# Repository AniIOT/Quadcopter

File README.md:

# Quadcopter
All files related to the quadcopter project will be added here, which include mechanical drawings, cad files, datasheets for motors, PCB designs, gerber files, component datasheets and footprint files, software files, libraries, reference docs etc.

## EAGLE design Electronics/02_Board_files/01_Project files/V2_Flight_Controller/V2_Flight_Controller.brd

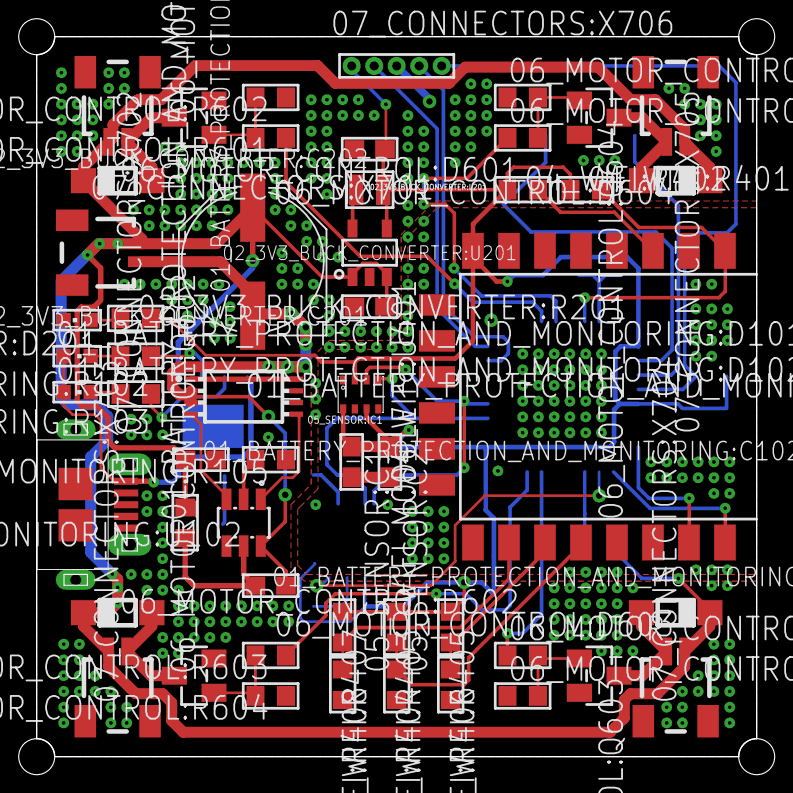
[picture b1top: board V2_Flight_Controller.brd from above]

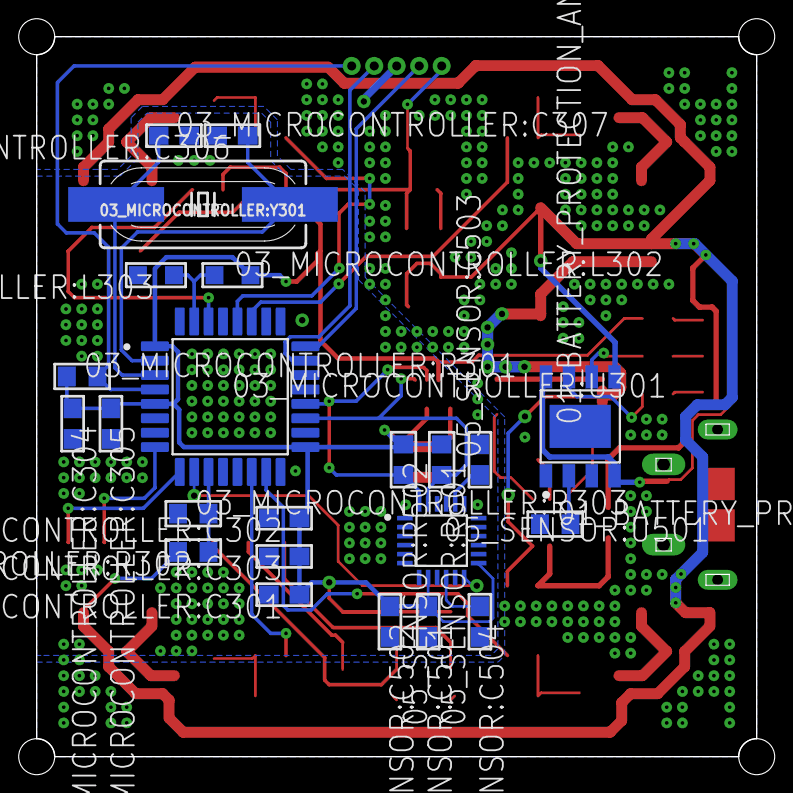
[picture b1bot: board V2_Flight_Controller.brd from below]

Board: 2 copper layers, 40.0 x 40.0 mm, 75 parts (23 on the bottom side), 48 nets.

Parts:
01_BATTERY_PROTECTION_AND_MONITORING:C101: 220uF; PANASONIC_E
01_BATTERY_PROTECTION_AND_MONITORING:C102, 02_3V3_BUCK_CONVERTER:C202: 10uF; C0603
01_BATTERY_PROTECTION_AND_MONITORING:C103: 0.1uF; C0603
01_BATTERY_PROTECTION_AND_MONITORING:D101: STDBY_GREEN; CHIPLED_0603
01_BATTERY_PROTECTION_AND_MONITORING:D102: CHRG_RED; CHIPLED_0603
01_BATTERY_PROTECTION_AND_MONITORING:R101: 4.8KΩ; R0603
01_BATTERY_PROTECTION_AND_MONITORING:R102, 01_BATTERY_PROTECTION_AND_MONITORING:R103, 01_BATTERY_PROTECTION_AND_MONITORING:R105, 02_3V3_BUCK_CONVERTER:R201, 06_MOTOR_CONTROL:R601, 06_MOTOR_CONTROL:R603, 06_MOTOR_CONTROL:R605, 06_MOTOR_CONTROL:R607: 1KΩ; R0603
01_BATTERY_PROTECTION_AND_MONITORING:R104: 100Ω; R0603
01_BATTERY_PROTECTION_AND_MONITORING:T101: DMN3024LSD; TSSOP-8
01_BATTERY_PROTECTION_AND_MONITORING:U101: TP4056; SOP-8
01_BATTERY_PROTECTION_AND_MONITORING:U102: DW01A; SOT23-6
02_3V3_BUCK_CONVERTER:C201, 03_MICROCONTROLLER:C304: 10nF; C0603
02_3V3_BUCK_CONVERTER:D201: 3V3_GREEN; CHIPLED_0603
02_3V3_BUCK_CONVERTER:L201: 2.2uH; SRN2009T-2R2M
02_3V3_BUCK_CONVERTER:U201: LM3670; SOT-23-5
03_MICROCONTROLLER:C301, 03_MICROCONTROLLER:C302: 100nF; C0603
03_MICROCONTROLLER:C303: 4.7uF; C0603
03_MICROCONTROLLER:C305: 1uF; C0603
03_MICROCONTROLLER:C306, 03_MICROCONTROLLER:C307: 20pF; C0603
03_MICROCONTROLLER:L302, 03_MICROCONTROLLER:L303: FERRITE BEAD; L2012C
03_MICROCONTROLLER:R301, 04_WIFI:R401, 04_WIFI:R402, 04_WIFI:R403, 04_WIFI:R404, 04_WIFI:R405, 04_WIFI:R406, 04_WIFI:R407, 04_WIFI:R408: 10KΩ; R0603
03_MICROCONTROLLER:R302: 2KΩ; R0603
03_MICROCONTROLLER:R303: 5KΩ; R0603
03_MICROCONTROLLER:U301: STM32F030K6T6; QFP80P900X900X160-32N
03_MICROCONTROLLER:Y301: 8MHz; HC49UP
04_WIFI:U401: WIFI_MODULE; ESP8266-ESP12E
05_SENSOR:C1, 05_SENSOR:C2: 100nF, 50V, ±10%; C0603
05_SENSOR:C501: 0.1uF, 4V, ±10%; C0603
05_SENSOR:C502: 10nF, 4V, ±10%; C0603
05_SENSOR:C503: 2.2nF, 50V, ±10%; C0603
05_SENSOR:C504: 0.1uF, 2V, ±10%; C0603
05_SENSOR:IC1: BMP280
05_SENSOR:R501, 05_SENSOR:R502: 4.7k; R0603
05_SENSOR:U501: MPU-6050; QFN50P400X400X95-24N
06_MOTOR_CONTROL:D601, 06_MOTOR_CONTROL:D602, 06_MOTOR_CONTROL:D603, 06_MOTOR_CONTROL:D604: 1N5819; SOD123
06_MOTOR_CONTROL:Q601, 06_MOTOR_CONTROL:Q602, 06_MOTOR_CONTROL:Q603, 06_MOTOR_CONTROL:Q604: SI2302; SOT23
06_MOTOR_CONTROL:R602, 06_MOTOR_CONTROL:R604, 06_MOTOR_CONTROL:R606, 06_MOTOR_CONTROL:R608: 4.7KΩ; R0603
07_CONNECTORS:J701: MICRO-USB; 47589-0001
07_CONNECTORS:X701: Battery Connector; SM02B-SRSS-TB
07_CONNECTORS:X702: Motor 1; SM02B-SRSS-TB
07_CONNECTORS:X703: Motor 2; SM02B-SRSS-TB
07_CONNECTORS:X704: Motor 3; SM02B-SRSS-TB
07_CONNECTORS:X705: Motor 4; SM02B-SRSS-TB
07_CONNECTORS:X706: JTAG; 53047-05

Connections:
01_BATTERY_PROTECTION_AND_MONITORING:CHRG: 01_BATTERY_PROTECTION_AND_MONITORING:R1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.1, 01_BATTERY_PROTECTION_AND_MONITORING:U1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.7
01_BATTERY_PROTECTION_AND_MONITORING:CHRG_LED: 01_BATTERY_PROTECTION_AND_MONITORING:D1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.C, 01_BATTERY_PROTECTION_AND_MONITORING:R1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.2
01_BATTERY_PROTECTION_AND_MONITORING:CS: 01_BATTERY_PROTECTION_AND_MONITORING:R1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.2, 01_BATTERY_PROTECTION_AND_MONITORING:U1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.2
01_BATTERY_PROTECTION_AND_MONITORING:D2S: 01_BATTERY_PROTECTION_AND_MONITORING:T1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.1, 01_BATTERY_PROTECTION_AND_MONITORING:T1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.8
01_BATTERY_PROTECTION_AND_MONITORING:OC: 01_BATTERY_PROTECTION_AND_MONITORING:T1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.4, 01_BATTERY_PROTECTION_AND_MONITORING:U1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.3
01_BATTERY_PROTECTION_AND_MONITORING:OD: 01_BATTERY_PROTECTION_AND_MONITORING:T1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.5, 01_BATTERY_PROTECTION_AND_MONITORING:U1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.1
01_BATTERY_PROTECTION_AND_MONITORING:PROG: 01_BATTERY_PROTECTION_AND_MONITORING:R1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.2, 01_BATTERY_PROTECTION_AND_MONITORING:U1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.2
01_BATTERY_PROTECTION_AND_MONITORING:STDBY: 01_BATTERY_PROTECTION_AND_MONITORING:R1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.1, 01_BATTERY_PROTECTION_AND_MONITORING:U1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.6
01_BATTERY_PROTECTION_AND_MONITORING:STDBY_LED: 01_BATTERY_PROTECTION_AND_MONITORING:D1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.C, 01_BATTERY_PROTECTION_AND_MONITORING:R1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.2
01_BATTERY_PROTECTION_AND_MONITORING:VCC: 01_BATTERY_PROTECTION_AND_MONITORING:C1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.1, 01_BATTERY_PROTECTION_AND_MONITORING:R1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.1, 01_BATTERY_PROTECTION_AND_MONITORING:U1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.5
02_3V3_BUCK_CONVERTER:LED_3V3: 02_3V3_BUCK_CONVERTER:D201.A, 02_3V3_BUCK_CONVERTER:R201.1
02_3V3_BUCK_CONVERTER:SW: 02_3V3_BUCK_CONVERTER:L201.1, 02_3V3_BUCK_CONVERTER:U201.5
03_MICROCONTROLLER:BAT_MON: 03_MICROCONTROLLER:R302.1, 03_MICROCONTROLLER:R303.2, 03_MICROCONTROLLER:U301.11
03_MICROCONTROLLER:BOOT0: 03_MICROCONTROLLER:L302.1, 03_MICROCONTROLLER:L303.1, 03_MICROCONTROLLER:U301.31
03_MICROCONTROLLER:XTAL_IN: 03_MICROCONTROLLER:C306.1, 03_MICROCONTROLLER:U301.2, 03_MICROCONTROLLER:Y301.1
03_MICROCONTROLLER:XTAL_OUT: 03_MICROCONTROLLER:C307.1, 03_MICROCONTROLLER:U301.3, 03_MICROCONTROLLER:Y301.2
04_WIFI:CH_PD: 04_WIFI:R402.2, 04_WIFI:U401.3
04_WIFI:GPIO0: 04_WIFI:R403.2, 04_WIFI:R404.1, 04_WIFI:U401.12
04_WIFI:GPIO2: 04_WIFI:R405.2, 04_WIFI:R406.1, 04_WIFI:U401.11
04_WIFI:GPIO15: 04_WIFI:R407.2, 04_WIFI:R408.1, 04_WIFI:U401.10
05_SENSOR:CPOUT: 05_SENSOR:C503.1, 05_SENSOR:U501.20
05_SENSOR:REGOUT: 05_SENSOR:C504.1, 05_SENSOR:U501.10
06_MOTOR_CONTROL:M1_GATE: 06_MOTOR_CONTROL:Q601.1, 06_MOTOR_CONTROL:R601.2, 06_MOTOR_CONTROL:R602.2
06_MOTOR_CONTROL:M2_GATE: 06_MOTOR_CONTROL:Q602.1, 06_MOTOR_CONTROL:R603.2, 06_MOTOR_CONTROL:R604.2
06_MOTOR_CONTROL:M3_GATE: 06_MOTOR_CONTROL:Q603.1, 06_MOTOR_CONTROL:R605.2, 06_MOTOR_CONTROL:R606.2
06_MOTOR_CONTROL:M4_GATE: 06_MOTOR_CONTROL:Q604.1, 06_MOTOR_CONTROL:R607.2, 06_MOTOR_CONTROL:R608.2
+3V3: 02_3V3_BUCK_CONVERTER:C202.1, 02_3V3_BUCK_CONVERTER:L201.2, 02_3V3_BUCK_CONVERTER:R201.2, 02_3V3_BUCK_CONVERTER:U201.4, 03_MICROCONTROLLER:C301.1, 03_MICROCONTROLLER:C302.1, 03_MICROCONTROLLER:C303.1, 03_MICROCONTROLLER:C304.1, 03_MICROCONTROLLER:C305.1, 03_MICROCONTROLLER:L302.2, 03_MICROCONTROLLER:R301.1, 03_MICROCONTROLLER:U301.1, 03_MICROCONTROLLER:U301.5, 03_MICROCONTROLLER:U301.17, 04_WIFI:R401.1, 04_WIFI:R402.1, 04_WIFI:R403.1, 04_WIFI:R405.1, 04_WIFI:R407.1, 04_WIFI:U401.8, 05_SENSOR:C1.1, 05_SENSOR:C2.1, 05_SENSOR:C501.1, 05_SENSOR:C502.1, 05_SENSOR:IC1.2, 05_SENSOR:IC1.6, 05_SENSOR:IC1.8, 05_SENSOR:R501.1, 05_SENSOR:R502.1, 05_SENSOR:U501.8, 05_SENSOR:U501.13, 07_CONNECTORS:X706.5
+5V: 01_BATTERY_PROTECTION_AND_MONITORING:D1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.A, 01_BATTERY_PROTECTION_AND_MONITORING:D1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.A, 01_BATTERY_PROTECTION_AND_MONITORING:U1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.4, 01_BATTERY_PROTECTION_AND_MONITORING:U1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.8, 07_CONNECTORS:J701.1
BATTERY_+VE: 01_BATTERY_PROTECTION_AND_MONITORING:C1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.+, 01_BATTERY_PROTECTION_AND_MONITORING:C1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.1, 01_BATTERY_PROTECTION_AND_MONITORING:R1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.2, 01_BATTERY_PROTECTION_AND_MONITORING:U1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.5, 02_3V3_BUCK_CONVERTER:C201.1, 02_3V3_BUCK_CONVERTER:U201.1, 02_3V3_BUCK_CONVERTER:U201.3, 03_MICROCONTROLLER:R302.2, 06_MOTOR_CONTROL:D601.C, 06_MOTOR_CONTROL:D602.C, 06_MOTOR_CONTROL:D603.C, 06_MOTOR_CONTROL:D604.C, 07_CONNECTORS:X701.1, 07_CONNECTORS:X702.2, 07_CONNECTORS:X703.1, 07_CONNECTORS:X704.2, 07_CONNECTORS:X705.1
BATTERY_-VE: 01_BATTERY_PROTECTION_AND_MONITORING:C1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.-, 01_BATTERY_PROTECTION_AND_MONITORING:C1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.2, 01_BATTERY_PROTECTION_AND_MONITORING:T1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.2, 01_BATTERY_PROTECTION_AND_MONITORING:T1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.3, 01_BATTERY_PROTECTION_AND_MONITORING:U1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.6, 07_CONNECTORS:X701.2
GND: 01_BATTERY_PROTECTION_AND_MONITORING:C1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.2, 01_BATTERY_PROTECTION_AND_MONITORING:R1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.1, 01_BATTERY_PROTECTION_AND_MONITORING:R1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.1, 01_BATTERY_PROTECTION_AND_MONITORING:T1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.6, 01_BATTERY_PROTECTION_AND_MONITORING:T1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.7, 01_BATTERY_PROTECTION_AND_MONITORING:U1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.1, 01_BATTERY_PROTECTION_AND_MONITORING:U1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.3, 02_3V3_BUCK_CONVERTER:C201.2, 02_3V3_BUCK_CONVERTER:C202.2, 02_3V3_BUCK_CONVERTER:D201.C, 02_3V3_BUCK_CONVERTER:U201.2, 03_MICROCONTROLLER:C301.2, 03_MICROCONTROLLER:C302.2, 03_MICROCONTROLLER:C303.2, 03_MICROCONTROLLER:C304.2, 03_MICROCONTROLLER:C305.2, 03_MICROCONTROLLER:C306.2, 03_MICROCONTROLLER:C307.2, 03_MICROCONTROLLER:L303.2, 03_MICROCONTROLLER:R303.1, 03_MICROCONTROLLER:U301.16, 03_MICROCONTROLLER:U301.32, 04_WIFI:R404.2, 04_WIFI:R406.2, 04_WIFI:R408.2, 04_WIFI:U401.9, 05_SENSOR:C1.2, 05_SENSOR:C2.2, 05_SENSOR:C501.2, 05_SENSOR:C502.2, 05_SENSOR:C503.2, 05_SENSOR:C504.2, 05_SENSOR:IC1.1, 05_SENSOR:IC1.5, 05_SENSOR:IC1.7, 05_SENSOR:U501.1, 05_SENSOR:U501.9, 05_SENSOR:U501.11, 05_SENSOR:U501.18, 06_MOTOR_CONTROL:Q601.2, 06_MOTOR_CONTROL:Q602.2, 06_MOTOR_CONTROL:Q603.2, 06_MOTOR_CONTROL:Q604.2, 06_MOTOR_CONTROL:R602.1, 06_MOTOR_CONTROL:R604.1, 06_MOTOR_CONTROL:R606.1, 06_MOTOR_CONTROL:R608.1, 07_CONNECTORS:J701.5, 07_CONNECTORS:J701.CASING1, 07_CONNECTORS:J701.CASING2, 07_CONNECTORS:J701.CASING3, 07_CONNECTORS:J701.CASING4, 07_CONNECTORS:X702.FIT@1, 07_CONNECTORS:X702.FIT@2, 07_CONNECTORS:X703.FIT@1, 07_CONNECTORS:X703.FIT@2, 07_CONNECTORS:X704.FIT@1, 07_CONNECTORS:X704.FIT@2, 07_CONNECTORS:X705.FIT@1, 07_CONNECTORS:X705.FIT@2, 07_CONNECTORS:X706.3
I2C_SCL: 03_MICROCONTROLLER:U301.19, 05_SENSOR:IC1.4, 05_SENSOR:R501.2, 05_SENSOR:U501.23
I2C_SDA: 03_MICROCONTROLLER:U301.20, 05_SENSOR:IC1.3, 05_SENSOR:R502.2, 05_SENSOR:U501.24
IMU_INT: 03_MICROCONTROLLER:U301.10, 05_SENSOR:U501.12
M1: 06_MOTOR_CONTROL:D601.A, 06_MOTOR_CONTROL:Q601.3, 07_CONNECTORS:X702.1
M1_PWM: 03_MICROCONTROLLER:U301.27, 06_MOTOR_CONTROL:R601.1
M2: 06_MOTOR_CONTROL:D602.A, 06_MOTOR_CONTROL:Q602.3, 07_CONNECTORS:X703.2
M2_PWM: 03_MICROCONTROLLER:U301.15, 06_MOTOR_CONTROL:R603.1
M3: 06_MOTOR_CONTROL:D603.A, 06_MOTOR_CONTROL:Q603.3, 07_CONNECTORS:X704.1
M3_PWM: 03_MICROCONTROLLER:U301.14, 06_MOTOR_CONTROL:R605.1
M4: 06_MOTOR_CONTROL:D604.A, 06_MOTOR_CONTROL:Q604.3, 07_CONNECTORS:X705.2
M4_PWM: 03_MICROCONTROLLER:U301.28, 06_MOTOR_CONTROL:R607.1
NRST: 03_MICROCONTROLLER:R301.2, 03_MICROCONTROLLER:U301.4, 07_CONNECTORS:X706.1
SWCLK: 03_MICROCONTROLLER:U301.24, 07_CONNECTORS:X706.4
SWDIO: 03_MICROCONTROLLER:U301.23, 07_CONNECTORS:X706.2
UART1_RX: 03_MICROCONTROLLER:U301.9, 04_WIFI:U401.16
UART1_TX: 03_MICROCONTROLLER:U301.8, 04_WIFI:U401.15
WIFI_RST: 03_MICROCONTROLLER:U301.30, 04_WIFI:R401.2, 04_WIFI:U401.1

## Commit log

2019-10-15 Created folder structure
2019-10-15 1. Created folder structure for electronics 2. Added uC and IMU related datasheets
2019-10-15 datasheets added in power section
2019-10-16 changed folder name
2019-10-16 added communication folder
2019-10-16 created folders for battery and 3v3 in power section
2019-10-16 1. added 3v3 circuit and datasheets 2. added uC circuit
2019-10-18 mechanical assembly
2019-10-22 added schematic and board files added used libraries
2019-10-22 list of mosfets.png
2019-10-22 Schematic changes
2019-10-26 added sheets for power section and motor driver
2019-11-03 1. Created hierarchical structure in schematic 2. Battery charging and protection circuit added 3. Added various eagle libraries
2019-11-04 1. added connectors 2. added imu_int 3. added block diagram linkages 4. overall clean up
2019-11-08 1. Completed schematic 2. Added/Created required libraries/footprints
2019-11-08 1. Made changes in a few libraries, and added new footprints/libraries 2. Placement progress - 80%
2019-11-11 1. 80% placement and 50% routing completed 2. Removed central two layers making the pcb a 2 layer pcb 3. Added resists in MPU-6050.lbr 4. Added dimensions in SRN2009T-2R2M.lbr
2019-11-12 1. Routing
2019-11-13 1. Removed unnecessary pads in usb port 2. Completed placement and routing of first prototype
2019-11-15 Started with v2 of pcb layout
2019-11-15 1. Added bmp180.lbr, made changes in 1.25pitch programming connector library 2. Added Datasheets/05_Motor_control/SI2302.pdf 3. Completed top placement for v2 pcb layout
2019-11-16 1. added a bigger input capacitor
2019-11-16 1. Completed placement and top routing
2019-11-16 1. Made changes in pin assignment to help easy routing 2. routed 60% board
2019-11-16 1. Minor changes in a few libraries 2. Completed whole routing, DRC remaining 3. Added no connect library
2019-11-17 1. Completed Routing, DRC and ERC 2. Double checked all connections, names and values 3. Started with silk screen
2019-11-18 1. Layer 21 tPlace changes made 2. Removed everything on Layer 51 tDocu
2019-12-08 changed via size and filled open areas with them
2019-12-26 1. Added libraries 2. Renamed GND vias 3. Created GND polygons
2019-12-28 1. Removed all DRC errors
2020-04-11 changed motor mount
2020-04-11 motor mount changes
2020-04-19 Added esp tools

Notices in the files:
parts and their libraries:
SparkFun-Clocks: Licensing: Creative Commons ShareAlike 4.0 International - https://creativecommons.org/licenses/by-sa/4.0
con-molex-usb: (C) 2014 Tomasz Boleslaw CEDRO, cederom@tlen.pl, http://www.tomek.cedro.info.
